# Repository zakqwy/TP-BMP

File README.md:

Black Magic Probe, Thinkpad remix

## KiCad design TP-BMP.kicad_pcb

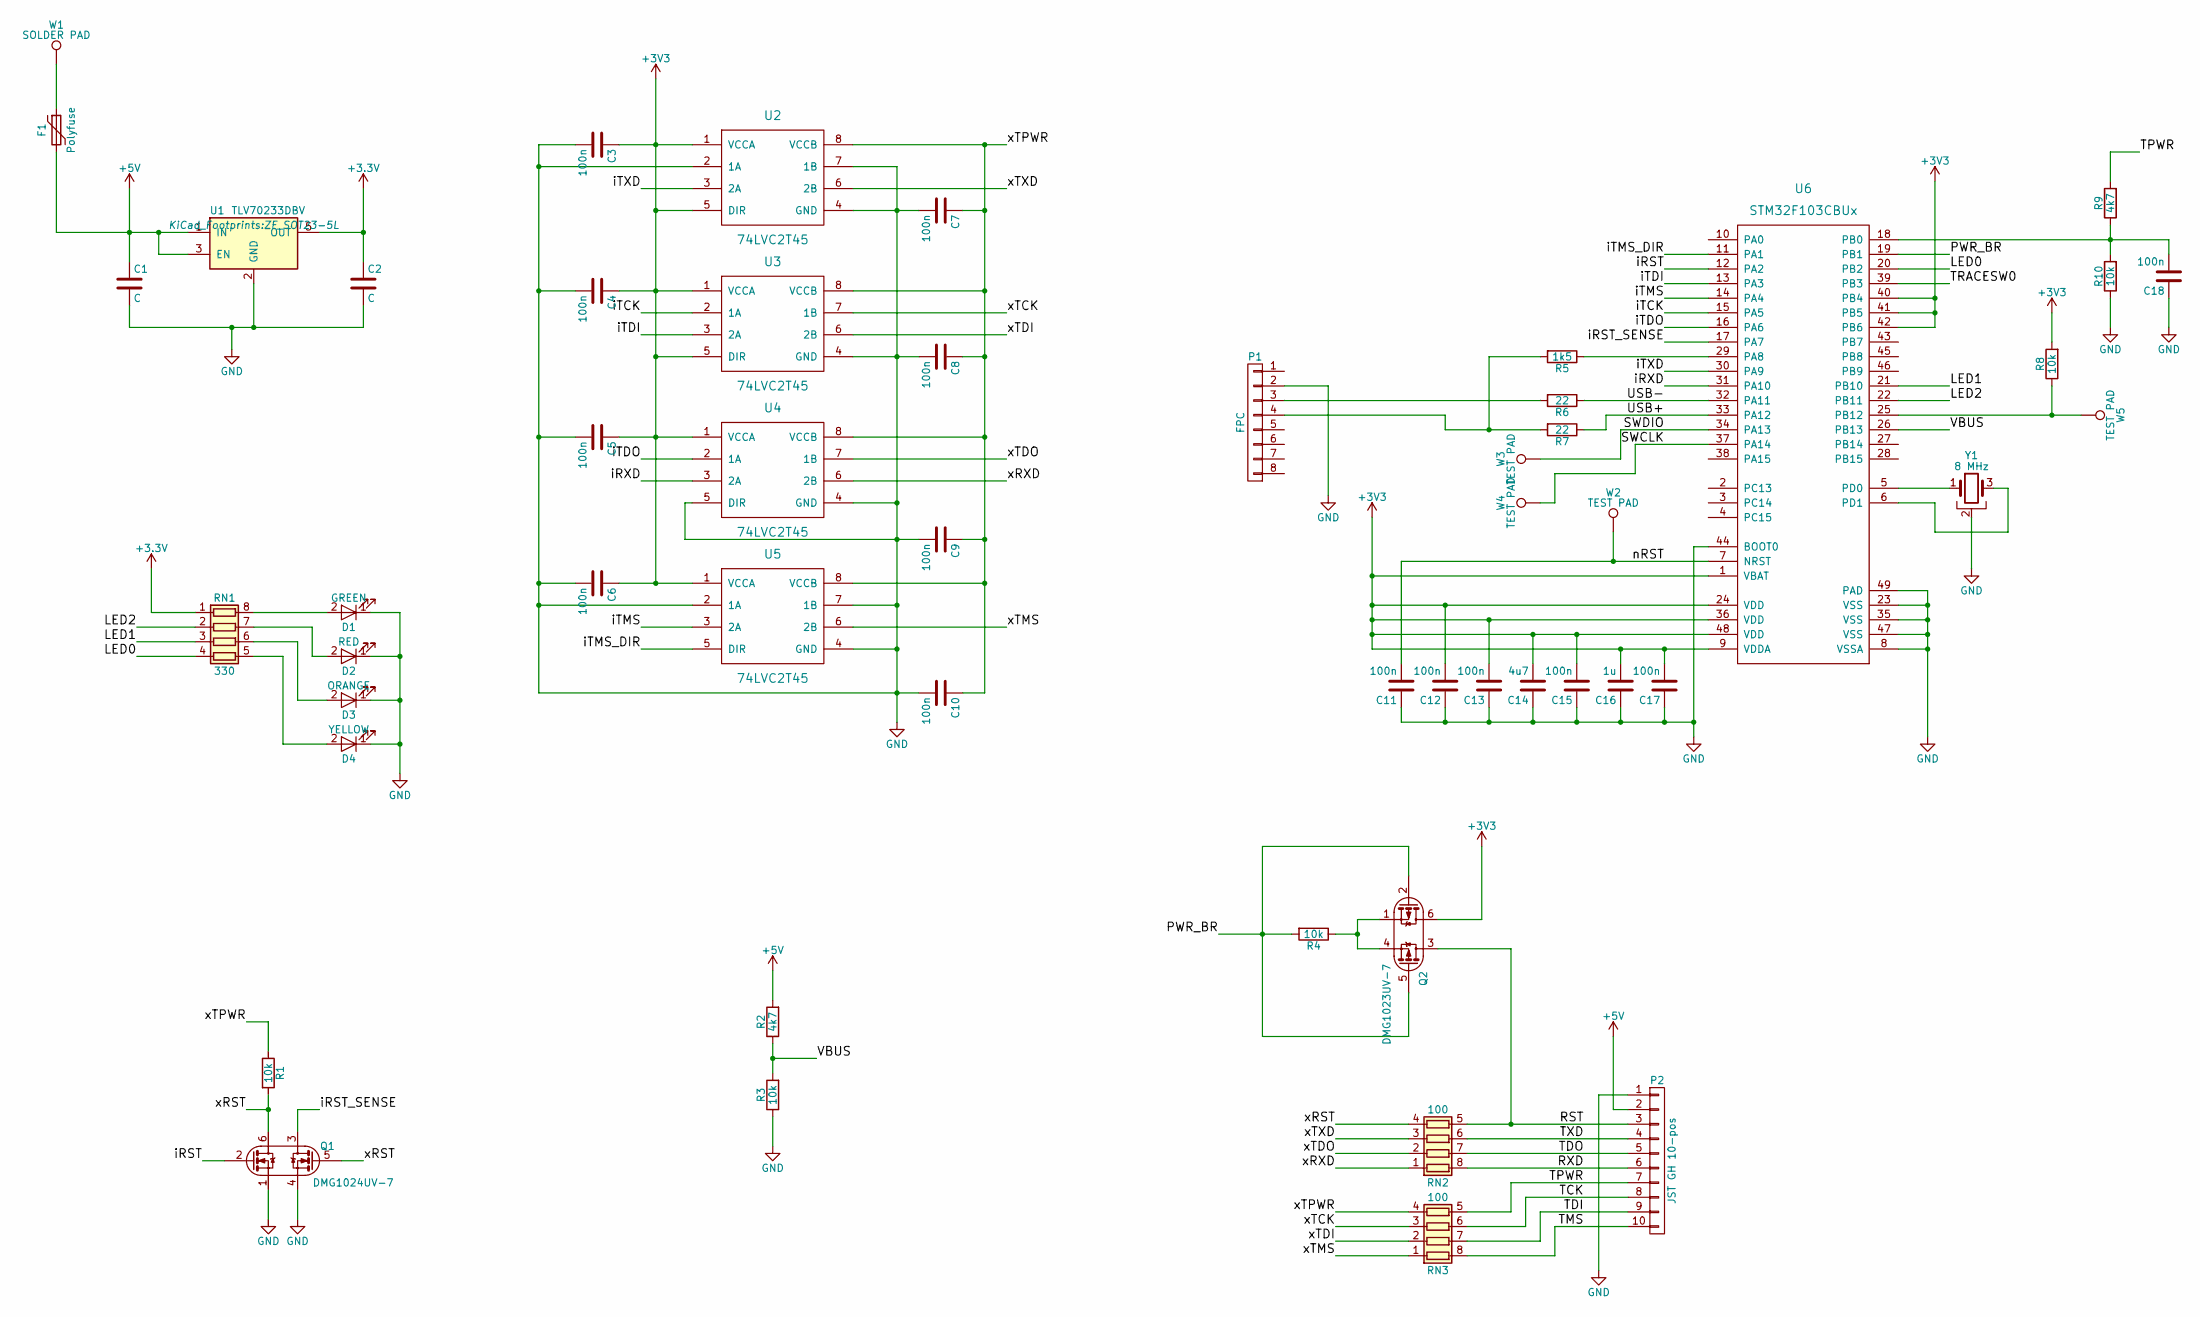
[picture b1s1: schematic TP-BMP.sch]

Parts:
C1, C2: C; ZF_SMD_NonPol_0603
C3, C4, C5, C6, C7, C8, C9, C10, C11, C12, C13, C15, C17, C18: 100n; ZF_SMD_NonPol_0402_cap
C14: 4u7; ZF_SMD_NonPol_0603
C16: 1u; ZF_SMD_NonPol_0603
D1: GREEN; ZF_SMD_NonPol_0402
D2: RED; ZF_SMD_NonPol_0402
D3: ORANGE; ZF_SMD_NonPol_0402
D4: YELLOW; ZF_SMD_NonPol_0402
F1: Polyfuse; ZF_SMD_nonpol_1206
P1: FPC; ZF_CONN_FPC_8POS_52745
P2: JST GH 10-pos; ZF_CONN_JST_GH_10POS
Q1: DMG1024UV-7; ZF_SMD_SOT-563
Q2: DMG1023UV-7; ZF_SMD_SOT-563
R1, R3, R4, R8, R10: 10k; ZF_SMD_NonPol_0402
R2, R9: 4k7; ZF_SMD_NonPol_0402
R5: 1k5; ZF_SMD_NonPol_0402
R6, R7: 22; ZF_SMD_NonPol_0402
RN1: 330; ZF_RN_4iso_CTS-0804
RN2, RN3: 100; ZF_RN_4iso_CTS-0804
U1: TLV70233DBV; ZF_SOT23-5L
U2, U3, U4, U5: 74LVC2T45; ZF_IC_XSON8
U6: STM32F103CBUx; ZF_IC_UFQFPN48
W1: SOLDER PAD; ZF_STRUCT_2.5x1
W2, W3, W4, W5: TEST PAD; ZF_CONN_1-2_pad
Y1: 8 MHz; ZF_XTAL_PBRV_M

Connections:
+5V: C1.1, F1.2, P2.2, R2.2, U1.1 (IN), U1.3 (EN)
/LED0: RN1.4 (R4.1), U6.20 (PB2)
/LED1: RN1.3 (R3.1), U6.21 (PB10)
/LED2: RN1.2 (R2.1), U6.22 (PB11)
/PWR_BR: Q2.2, Q2.5, R4.2, U6.19 (PB1)
/RST: P2.3, Q2.3, RN2.5 (R4.2)
/RXD: P2.6, RN2.8 (R1.2)
/SWCLK: U6.37 (PA14), W4.1
/SWDIO: U6.34 (PA13), W3.1
/TCK: P2.8, RN3.6 (R3.2)
/TDI: P2.9, RN3.7 (R2.2)
/TDO: P2.5, RN2.7 (R2.2)
/TMS: P2.10, RN3.8 (R1.2)
/TPWR: P2.7, R9.2, RN3.5 (R4.2)
/TRACESW0: U6.39 (PB3)
/TXD: P2.4, RN2.6 (R3.2)
/USB+: R7.1, U6.33 (PA12)
/USB-: R6.1, U6.32 (PA11)
/VBUS: R2.1, R3.2, U6.26 (PB13)
/iRST: Q1.2, U6.12 (PA2)
/iRST_SENSE: Q1.3, U6.17 (PA7)
/iRXD: U4.3 (2A), U6.31 (PA10)
/iTCK: U3.2 (1A), U6.15 (PA5)
/iTDI: U3.3 (2A), U6.13 (PA3)
/iTDO: U4.2 (1A), U6.16 (PA6)
/iTMS: U5.3 (2A), U6.14 (PA4)
/iTMS_DIR: U5.5 (DIR), U6.11 (PA1)
/iTXD: U2.3 (2A), U6.30 (PA9)
/nRST: C11.2, U6.7 (NRST), W2.1
/xRST: Q1.5, Q1.6, R1.2, RN2.4 (R4.1)
/xRXD: RN2.1 (R1.1), U4.6 (2B)
/xTCK: RN3.3 (R3.1), U3.7 (1B)
/xTDI: RN3.2 (R2.1), U3.6 (2B)
/xTDO: RN2.2 (R2.1), U4.7 (1B)
/xTMS: RN3.1 (R1.1), U5.6 (2B)
/xTPWR: C7.1, C8.1, C9.1, C10.1, R1.1, RN3.4 (R4.1), U2.8 (VCCB), U3.8 (VCCB), U4.8 (VCCB), U5.8 (VCCB)
/xTXD: RN2.3 (R3.1), U2.6 (2B)
GND: C1.2, C2.2, C3.2, C4.2, C5.2, C6.2, C7.2, C8.2, C9.2, C10.2, C11.1, C12.1, C13.1, C14.1, C15.1, C16.1, C17.1, C18.1, D1.1 (K), D2.1 (K), D3.1 (K), D4.1 (K), P1.2, P2.1, Q1.1, Q1.4, R3.1, R10.1, U1.2 (GND), U2.2 (1A), U2.4 (GND), U2.7 (1B), U3.4 (GND), U4.4 (GND), U4.5 (DIR), U5.2 (1A), U5.4 (GND), U5.7 (1B), U6.8 (VSSA), U6.23 (VSS), U6.35 (VSS), U6.44 (BOOT0), U6.47 (VSS), U6.49 (PAD), Y1.2
unnamed: C18.2, R9.1, R10.2, U6.18 (PB0)
unnamed: D1.2 (A), RN1.8 (R1.2)
unnamed: D2.2 (A), RN1.7 (R2.2)
unnamed: D3.2 (A), RN1.6 (R3.2)
unnamed: D4.2 (A), RN1.5 (R4.2)
unnamed: F1.1, W1.1
unnamed: P1.3, R6.2
unnamed: P1.4, R5.2, R7.2
unnamed: Q2.1, Q2.4, R4.1
unnamed: R5.1, U6.29 (PA8)
unnamed: R8.1, U6.25 (PB12), W5.1
unnamed: U6.5 (PD0), Y1.1
unnamed: U6.6 (PD1), Y1.3

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
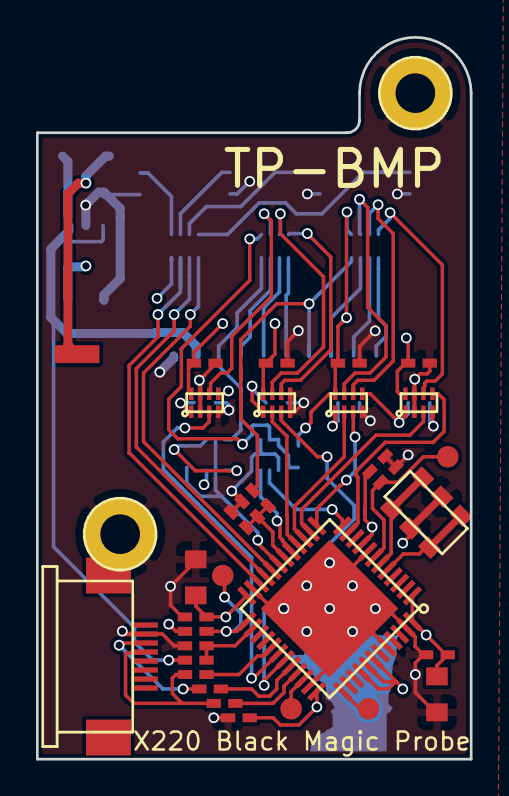
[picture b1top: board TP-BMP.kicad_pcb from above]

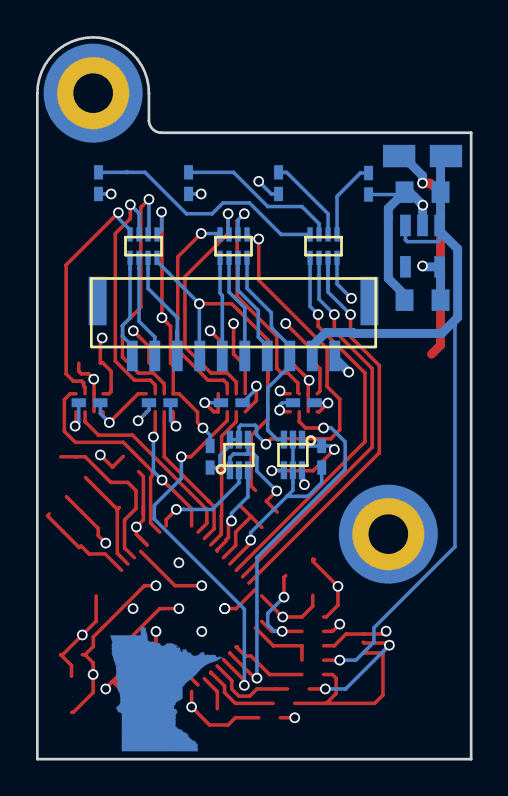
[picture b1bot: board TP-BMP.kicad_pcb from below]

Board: 4 copper layers, 24.1 x 40.1 mm, 52 parts (20 on the bottom side), 51 nets.

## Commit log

2017-08-19 Recreated BMP v2.1 schematic. Got most footprints sorted and created PCB outline.
2017-08-23 Finished rev 0.1 PCB and ordered. Not yet tested. 4-layer design fit-checked with cardboard vs X220. Should be compatible with BMP v2.1.
2017-09-13 added license, gitignore, and readme

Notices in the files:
TP-BMP.sch:
License: CC-BY-SA 4.0
(C) 2017 by Zach Fredin
